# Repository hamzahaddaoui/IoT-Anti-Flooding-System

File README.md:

# IoT Anti flooding

The designed anti-flooding system has the task of constantly monitoring certain parameters within a room where tests are carried out on coffee machines.
7 anti-flood sensors have been used, 5 mounted under each coffee machine, and 2 below the delivery pipe.
Furthermore, there is a pressure switch, in charge of measuring the water pressure and a volumetric meter, measuring the current water consumption. 
The system has the task of interrupting, through two solenoid valves, the water flow when one or more anomalies occur, including:
• Decrease in water pressure
• High water consumption
• Detection of water leaks (via flood sensors)
The sensors and devices are monitored via an electronic board (or via an electronic board by removing one) and, in the event of an anomaly, the two solenoid valves can also be deactivated by the board itself.
The control unit also sends the data related to each single sensor to a server, in order to be able to carry out a remote control. It is possible to check in any moment the situation of the system, and perform some actions.

### Board

### Electronics schematic

### Electrical schematic

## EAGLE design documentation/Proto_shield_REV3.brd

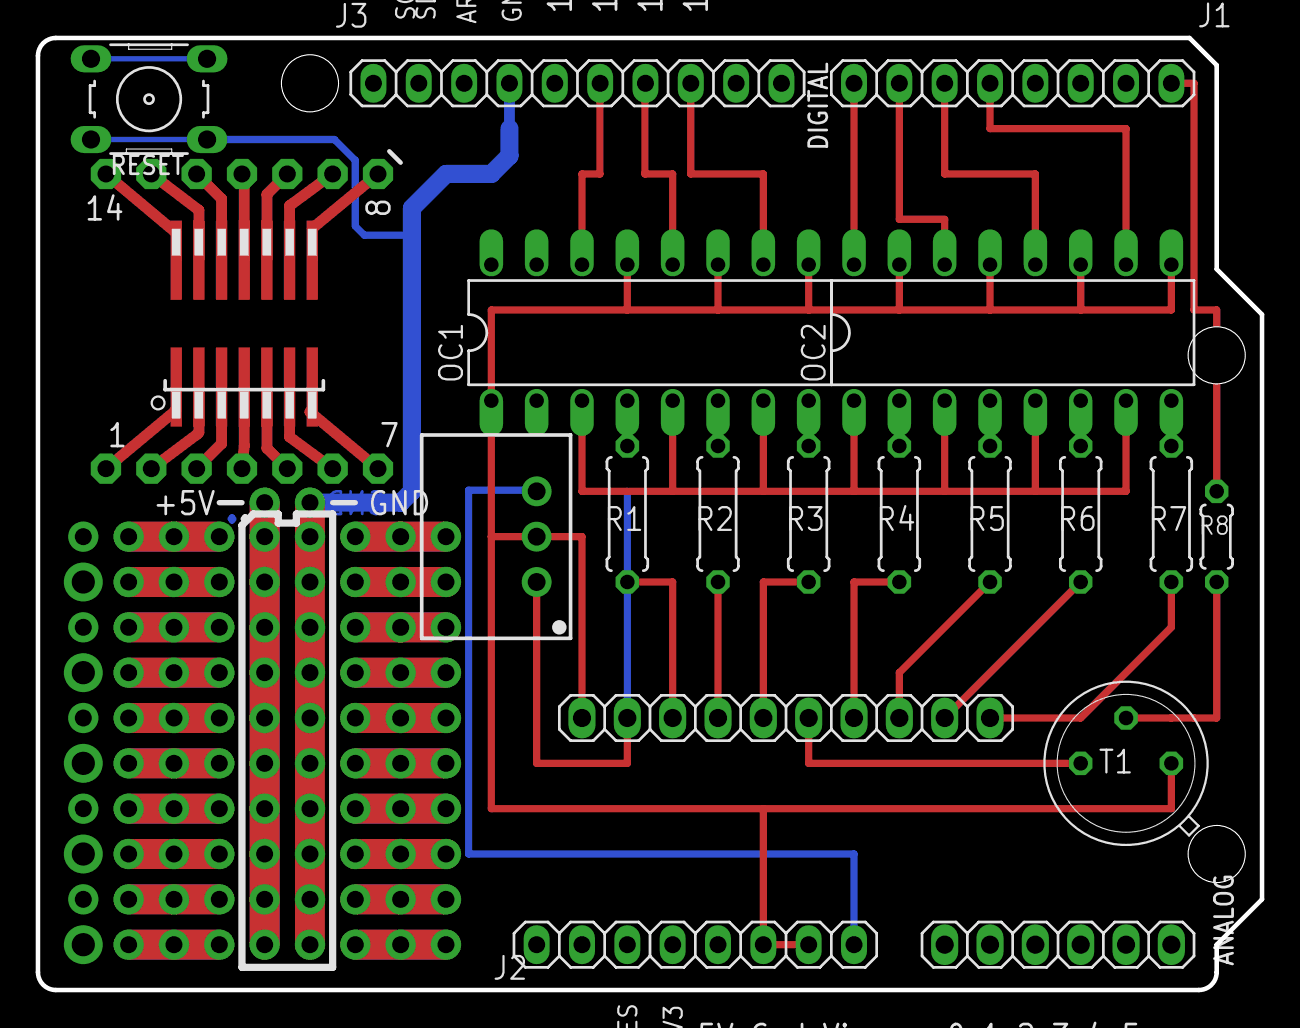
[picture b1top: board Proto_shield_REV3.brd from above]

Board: 2 copper layers, 68.6 x 53.3 mm, 33 parts (0 on the bottom side), 40 nets.

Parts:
1, 2, 3, 4, 5, 6, 7, 8, 9, 10, 11, 12, 13, 14: LSP10
12V/5V: SIP3
ANALOG: 1X06
E$13: 1X10
IC2: SMD-14; SO-14NMW
J1, J2: 1X08-TH
J3: 1X10-TH
OC1, OC2: DIL16
R1, R2: 10K x 7; 0207/7
R3, R4, R5, R6, R7: 10K; 0207/7
R8: 0204/5
RESET: B3F-10XX
T1: TO5

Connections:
GND: 12V/5V.2, E$13.1, J2.7, OC1.9, OC1.11, OC1.13, OC2.9, OC2.11, OC2.13, OC2.15, T1.1
unnamed: 14.MP, IC2.P$14
unnamed: 13.MP, IC2.P$13
unnamed: 12.MP, IC2.P$12
unnamed: 11.MP, IC2.P$11
unnamed: 10.MP, IC2.P$10
unnamed: 9.MP, IC2.P$9
unnamed: 8.MP, IC2.P$8
unnamed: 7.MP, IC2.P$7
unnamed: 6.MP, IC2.P$6
unnamed: 5.MP, IC2.P$5
unnamed: 3.MP, IC2.P$3
unnamed: 2.MP, IC2.P$2
unnamed: 1.MP, IC2.P$1
unnamed: 4.MP, IC2.P$4
S$2: OC2.8, R7.2
S$3: OC1.4, R1.2
S$4: OC1.6, R2.2
S$5: OC1.8, R3.2
S$6: OC2.2, R4.2
S$7: OC2.4, R5.2
S$8: OC2.6, R6.2
S$9: OC1.3, OC1.5, OC1.7, OC2.1, OC2.3, OC2.5, OC2.7
S$10: E$13.6, T1.3
S$11: J3.7, RESET.1, RESET.2
S$12: E$13.3, R1.1
S$13: E$13.10, R7.1
S$14: RESET.3, RESET.4
S$15: 12V/5V.1, E$13.2
S$16: E$13.4, R2.1
S$17: E$13.5, R3.1
S$19: J1.1, R8.2
S$20: R8.1, T1.2
S$23: J1.8, OC2.16
S$24: J1.7, OC2.14
S$25: E$13.7, R4.1
S$26: E$13.8, R5.1
S$27: E$13.9, R6.1
S$29: J1.6, OC2.12
S$30: J1.5, OC2.10
